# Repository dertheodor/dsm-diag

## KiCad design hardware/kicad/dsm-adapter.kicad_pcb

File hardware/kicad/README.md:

# Nano adapter PCB

A two-layer board for the [Nano adapter](../nano-adapter.md): 48 × 55 mm, through-hole parts only.

The scripts generate `dsm-adapter.kicad_sch` and `dsm-adapter.kicad_pcb`. Do not edit
the two files in KiCad: the next build overwrites them. Change the scripts instead.

| File | Owns |
|---|---|
| `generate_sch.py` | Parts, values and connections |
| `generate_pcb.py` | Placement, tracks, the ground pour and the silkscreen. It takes the nets from the schematic. |
| `build.sh` | Generates both files, runs ERC and DRC, and writes `out/` |

## Build

Run `hardware/kicad/build.sh`. It needs KiCad 10 with `kicad-cli` and the `pcbnew` Python module.

The script stops on any ERC or DRC violation and on any difference between the schematic and the board.

| Output | Use |
|---|---|
| `out/dsm-adapter-gerbers.zip` | Upload to the board maker |
| `out/dsm-adapter-schematic.pdf` | Schematic to print |
| `dsm-adapter-top.png`, `out/dsm-adapter-bottom.png` | 3D renders |

## Order

Upload the zip to JLCPCB, PCBWay or Aisler. The defaults fit:

- 2 layers, 1.6 mm FR-4, 1 oz copper
- HASL or ENIG finish
- Any solder mask colour

## Parts

| Ref | Part |
|---|---|
| A1 | Arduino Nano or clone, ATmega328P at 16 MHz. Use two 15-pin female headers, 2.54 mm, so the Nano stays removable. |
| R1, R2 | 10k, 1/4 W, 0207 body |
| R4 | 1k, 1/4 W, 0207 body |
| R5 | 2k, 1/4 W, 0207 body |
| J1 | 2-pin screw terminal, 5.0 mm pitch (Phoenix MKDS 1,5/2 footprint) |
| H1–H3 | M3 holes for a housing |

J1 takes the cable to the 12-pin plug. The silkscreen marks the car pins: pin 1 on the left, pin 12 on the right.

## Status

DRC and ERC pass. Nobody has ordered or tested this board yet.
Before you order, compare the Nano pinout of your clone with the footprint: D3, D4 and D5 are pads 6, 7 and 8.

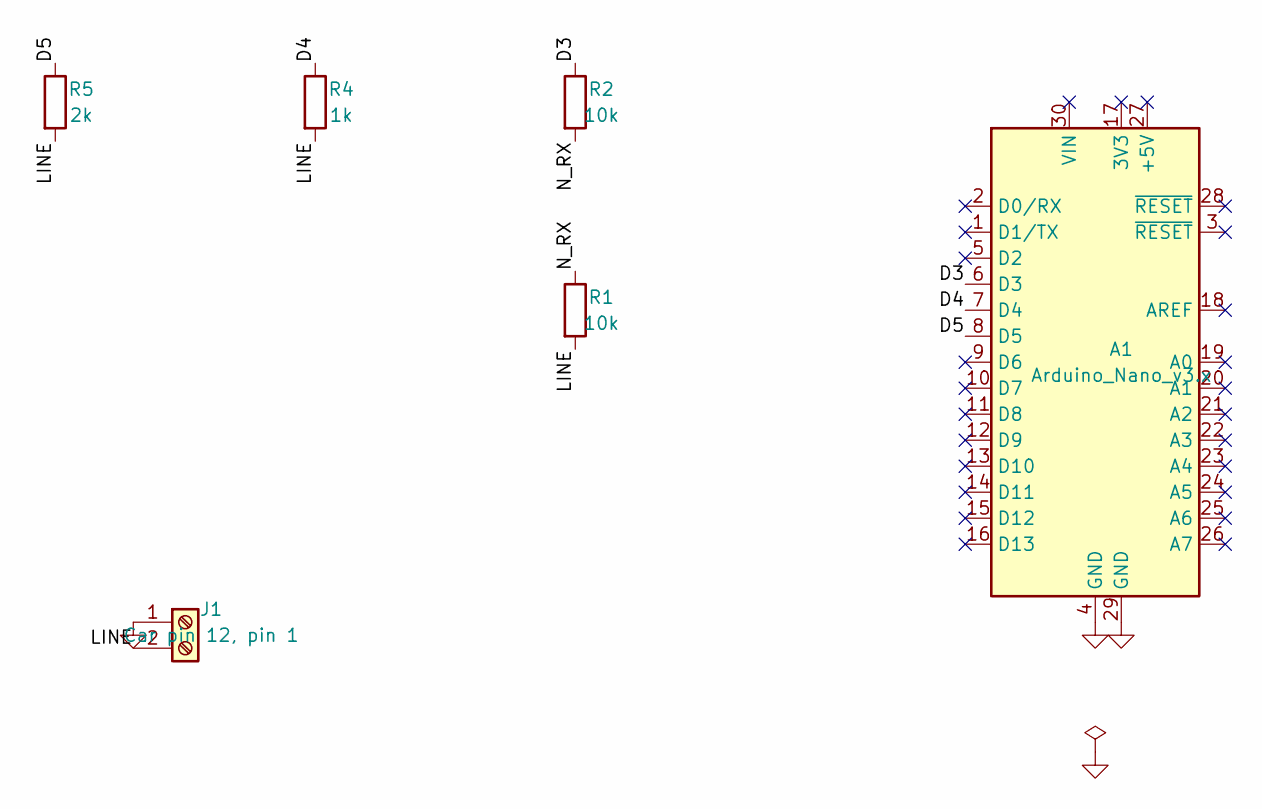
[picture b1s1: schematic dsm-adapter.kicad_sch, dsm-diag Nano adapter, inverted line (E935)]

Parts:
A1: Arduino_Nano_v3.x; Arduino_Nano
J1: Car pin 12, pin 1; TerminalBlock_Phoenix_MKDS-1,5-2_1x02_P5.00mm_Horizontal
R1, R2: 10k; R_Axial_DIN0207_L6.3mm_D2.5mm_P10.16mm_Horizontal
R4: 1k; R_Axial_DIN0207_L6.3mm_D2.5mm_P10.16mm_Horizontal
R5: 2k; R_Axial_DIN0207_L6.3mm_D2.5mm_P10.16mm_Horizontal

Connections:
/D3: A1.6 (D3), R2.1
/D4: A1.7 (D4), R4.1
/D5: A1.8 (D5), R5.1
/LINE: J1.2, R1.2, R4.2, R5.2
/N_RX: R1.1, R2.2
GND: A1.4 (GND), A1.29 (GND), J1.1

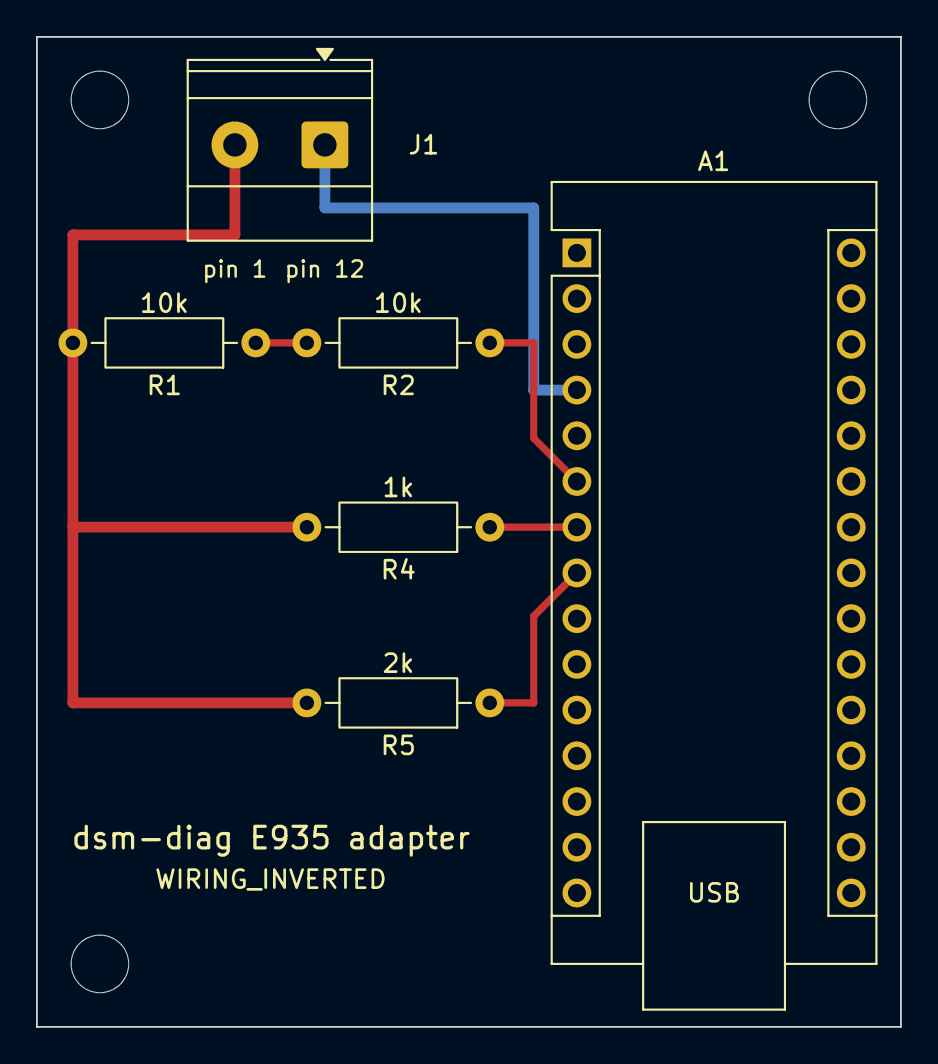
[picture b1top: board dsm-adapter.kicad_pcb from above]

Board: 2 copper layers, 48.0 x 55.0 mm, 9 parts (0 on the bottom side), 6 nets.

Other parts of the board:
H1, H2, H3: M3; MountingHole_3.2mm_M3
